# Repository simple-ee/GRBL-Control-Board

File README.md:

# GRBL-Control-Board
Custom GRBL cnc machine control board with quality in mind

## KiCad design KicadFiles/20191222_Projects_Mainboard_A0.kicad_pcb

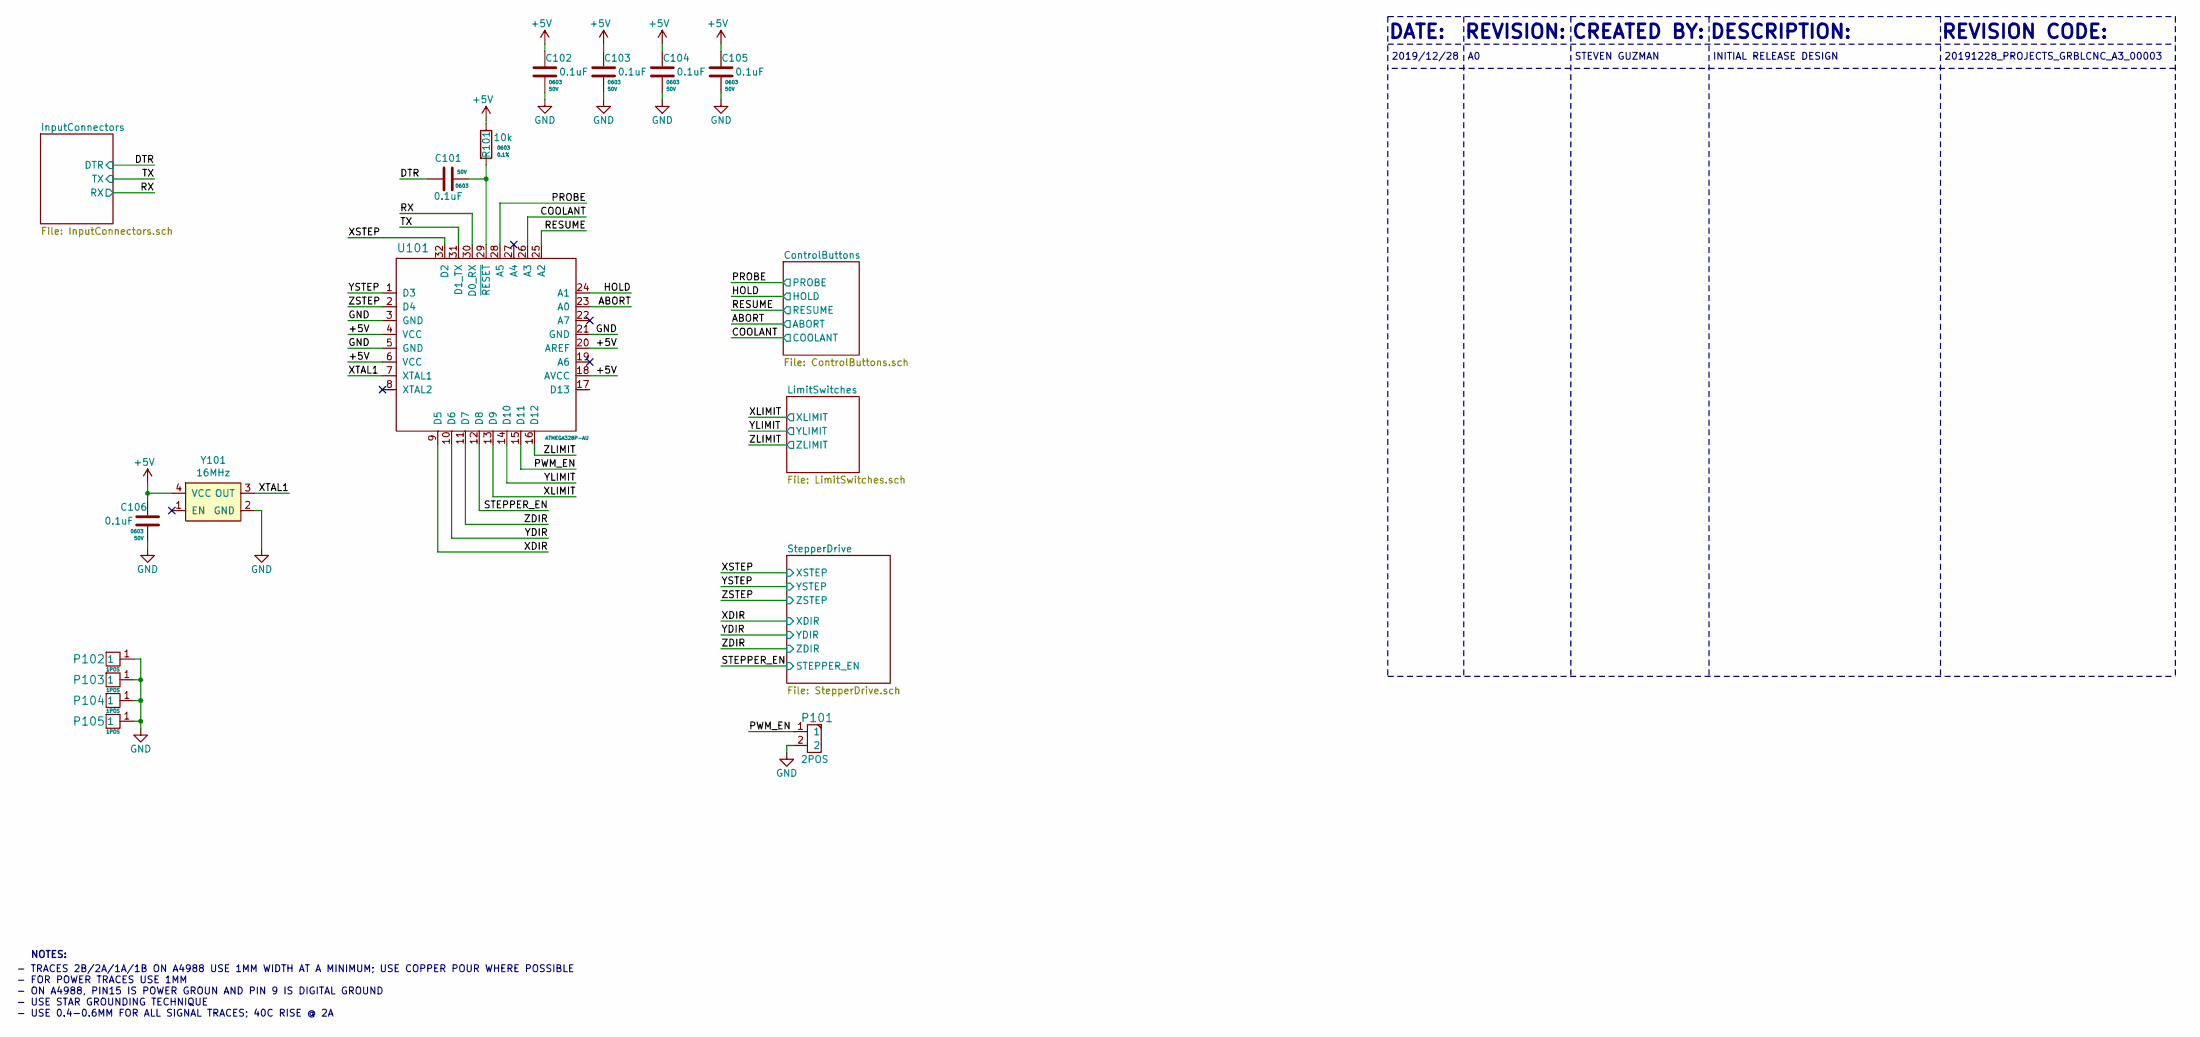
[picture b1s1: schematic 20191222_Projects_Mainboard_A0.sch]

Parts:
C101, C102, C103, C104, C105, C106: C0603C104K5RACAUTO; C_0603_Handsolder
P101: TH_2POS_2.54MM
P102, P103, P104, P105: TH_1POS_2.4MM_M2; TH_1POS_2.4MMxM2
R101: ERA-3AEB103V; R_0603_Handsolder
U101: ATMEGA328P-AU; TQFP-32
Y101: CB3-3I-16M0000; CB3

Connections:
+5V: C102.1, C103.1, C104.1, C105.1, C106.1, R101.1, U101.4 (VCC), U101.6 (VCC), U101.18 (AVCC), U101.20 (AREF), Y101.4 (VCC); also elsewhere on the board
/ABORT: U101.23 (A0); also elsewhere on the board
/COOLANT: U101.26 (A3); also elsewhere on the board
/DTR: C101.2; also elsewhere on the board
/HOLD: U101.24 (A1); also elsewhere on the board
/PROBE: U101.28 (A5); also elsewhere on the board
/PWM_EN: P101.1, U101.15 (D11)
/RESUME: U101.25 (A2); also elsewhere on the board
/RX: U101.30 (D0_RX); also elsewhere on the board
/STEPPER_EN: U101.12 (D8); also elsewhere on the board
/TX: U101.31 (D1_TX); also elsewhere on the board
/XDIR: U101.9 (D5); also elsewhere on the board
/XLIMIT: U101.13 (D9); also elsewhere on the board
/XSTEP: U101.32 (D2); also elsewhere on the board
/XTAL1: U101.7 (XTAL1), Y101.3 (OUT)
/YDIR: U101.10 (D6); also elsewhere on the board
/YLIMIT: U101.14 (D10); also elsewhere on the board
/YSTEP: U101.1 (D3); also elsewhere on the board
/ZDIR: U101.11 (D7); also elsewhere on the board
/ZLIMIT: U101.16 (D12); also elsewhere on the board
/ZSTEP: U101.2 (D4); also elsewhere on the board
GND: C102.2, C103.2, C104.2, C105.2, C106.2, P101.2, P102.1, P103.1, P104.1, P105.1, U101.3 (GND), U101.5 (GND), U101.21 (GND), Y101.2 (GND); also elsewhere on the board
unnamed: C101.1, R101.2, U101.29 (~RESET~)

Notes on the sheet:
DATE:
DESCRIPTION:
REVISION:
REVISION CODE:
2019/12/28
CREATED BY:
STEVEN GUZMAN
INITIAL RELEASE DESIGN
20191228_PROJECTS_GRBLCNC_A3_00003
- TRACES 2B/2A/1A/1B ON A4988 USE 1MM WIDTH AT A MINIMUM; USE COPPER POUR WHERE POSSIBLE - FOR POWER TRACES USE 1MM - ON A4988, PIN15 IS POWER GROUN AND PIN 9 IS DIGITAL GROUND - USE STAR GROUNDING TECHNIQUE - USE 0.4-0.6MM FOR ALL SIGNAL TRACES; 40C RISE @ 2A
NOTES:

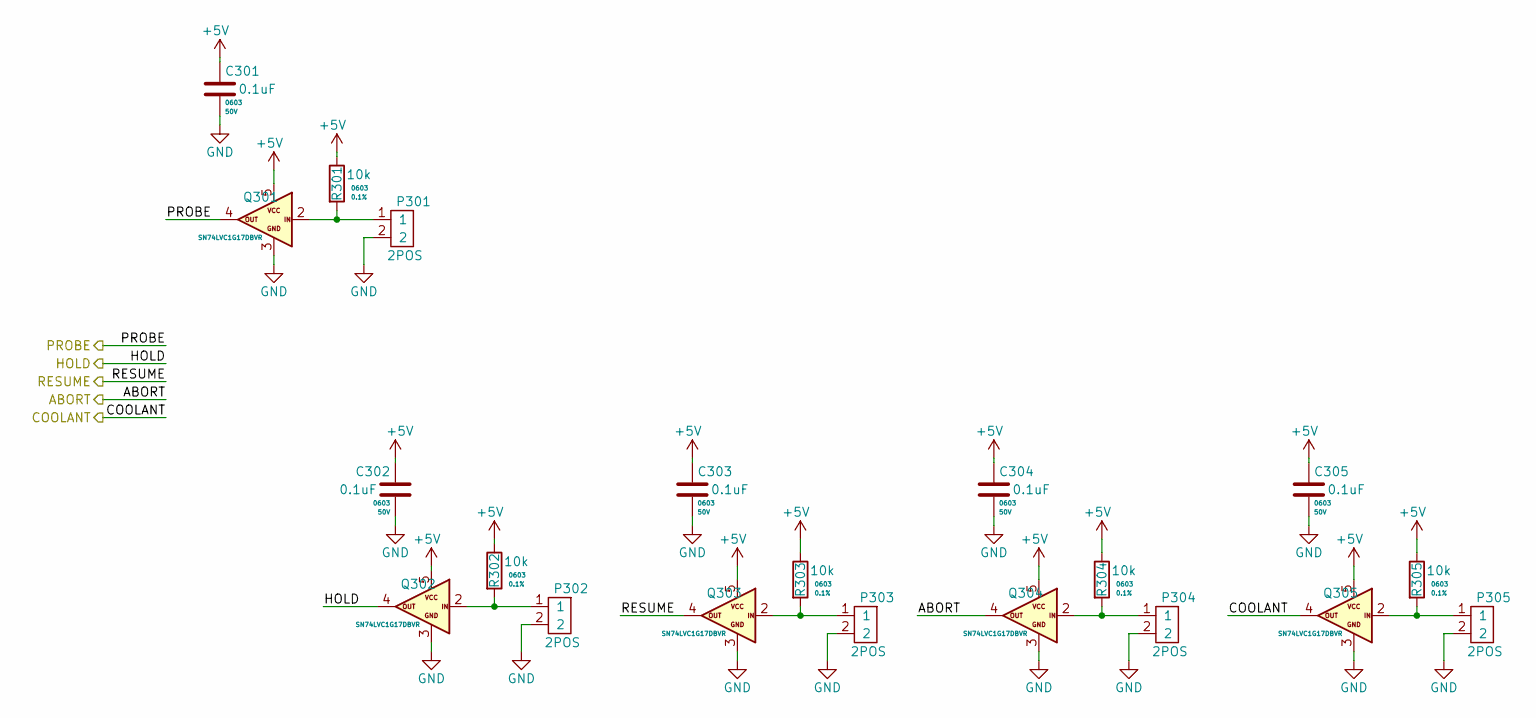
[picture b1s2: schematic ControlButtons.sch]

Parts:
C301, C302, C303, C304, C305: C0603C104K5RACAUTO; C_0603_Handsolder
P301, P302, P303, P304, P305: 2-1971798-4; 2-1971798
Q301, Q302, Q303, Q304, Q305: SN74LVC1G17DBVR; SOT-23-5_HandSoldering
R301, R302, R303, R304, R305: ERA-3AEB103V; R_0603_Handsolder

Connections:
+5V: C301.1, C302.1, C303.1, C304.1, C305.1, Q301.5, Q302.5, Q303.5, Q304.5, Q305.5, R301.1, R302.1, R303.1, R304.1, R305.1; also elsewhere on the board
/ABORT: Q304.4; also elsewhere on the board
/COOLANT: Q305.4; also elsewhere on the board
/HOLD: Q302.4; also elsewhere on the board
/PROBE: Q301.4; also elsewhere on the board
/RESUME: Q303.4; also elsewhere on the board
GND: C301.2, C302.2, C303.2, C304.2, C305.2, P301.2, P302.2, P303.2, P304.2, P305.2, Q301.3, Q302.3, Q303.3, Q304.3, Q305.3; also elsewhere on the board
unnamed: P301.1, Q301.2, R301.2
unnamed: P302.1, Q302.2, R302.2
unnamed: P303.1, Q303.2, R303.2
unnamed: P304.1, Q304.2, R304.2
unnamed: P305.1, Q305.2, R305.2

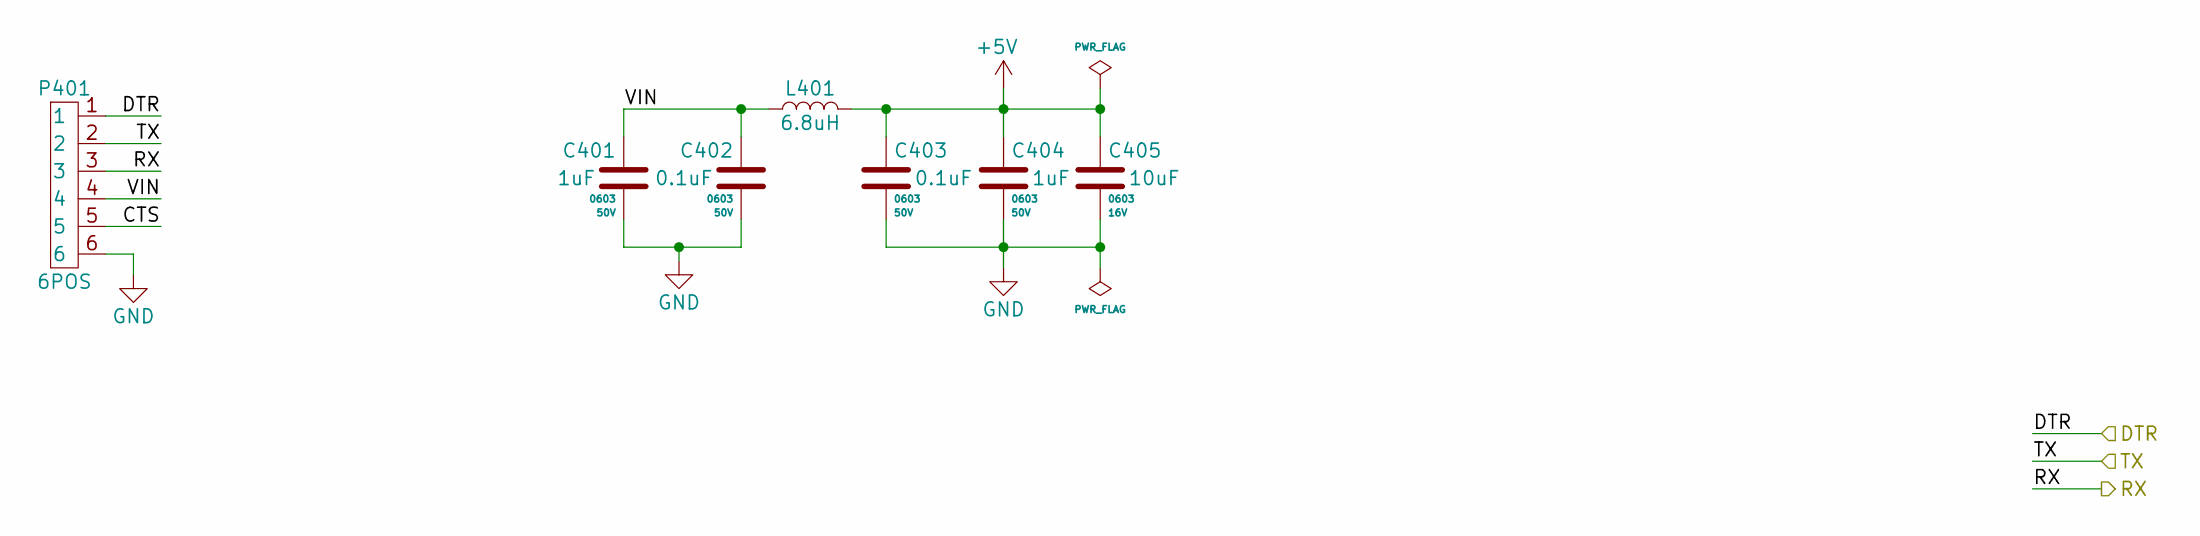
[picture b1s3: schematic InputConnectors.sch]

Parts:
C401, C404: CL10A105KB8NNNC; C_0603_Handsolder
C402, C403: C0603C104K5RACAUTO; C_0603_Handsolder
C405: CL10X106MO8NRNC; C_0603_Handsolder
L401: LPS6235-682MR_0; LPS6235
P401: M20-7910642R; M20

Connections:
+5V: C403.1, C404.1, C405.1, L401.2; also elsewhere on the board
/DTR: P401.1; also elsewhere on the board
/InputConnectors/VIN: C401.1, C402.1, L401.1, P401.4
/RX: P401.3; also elsewhere on the board
/TX: P401.2; also elsewhere on the board
GND: C401.2, C402.2, C403.2, C404.2, C405.2, P401.6; also elsewhere on the board

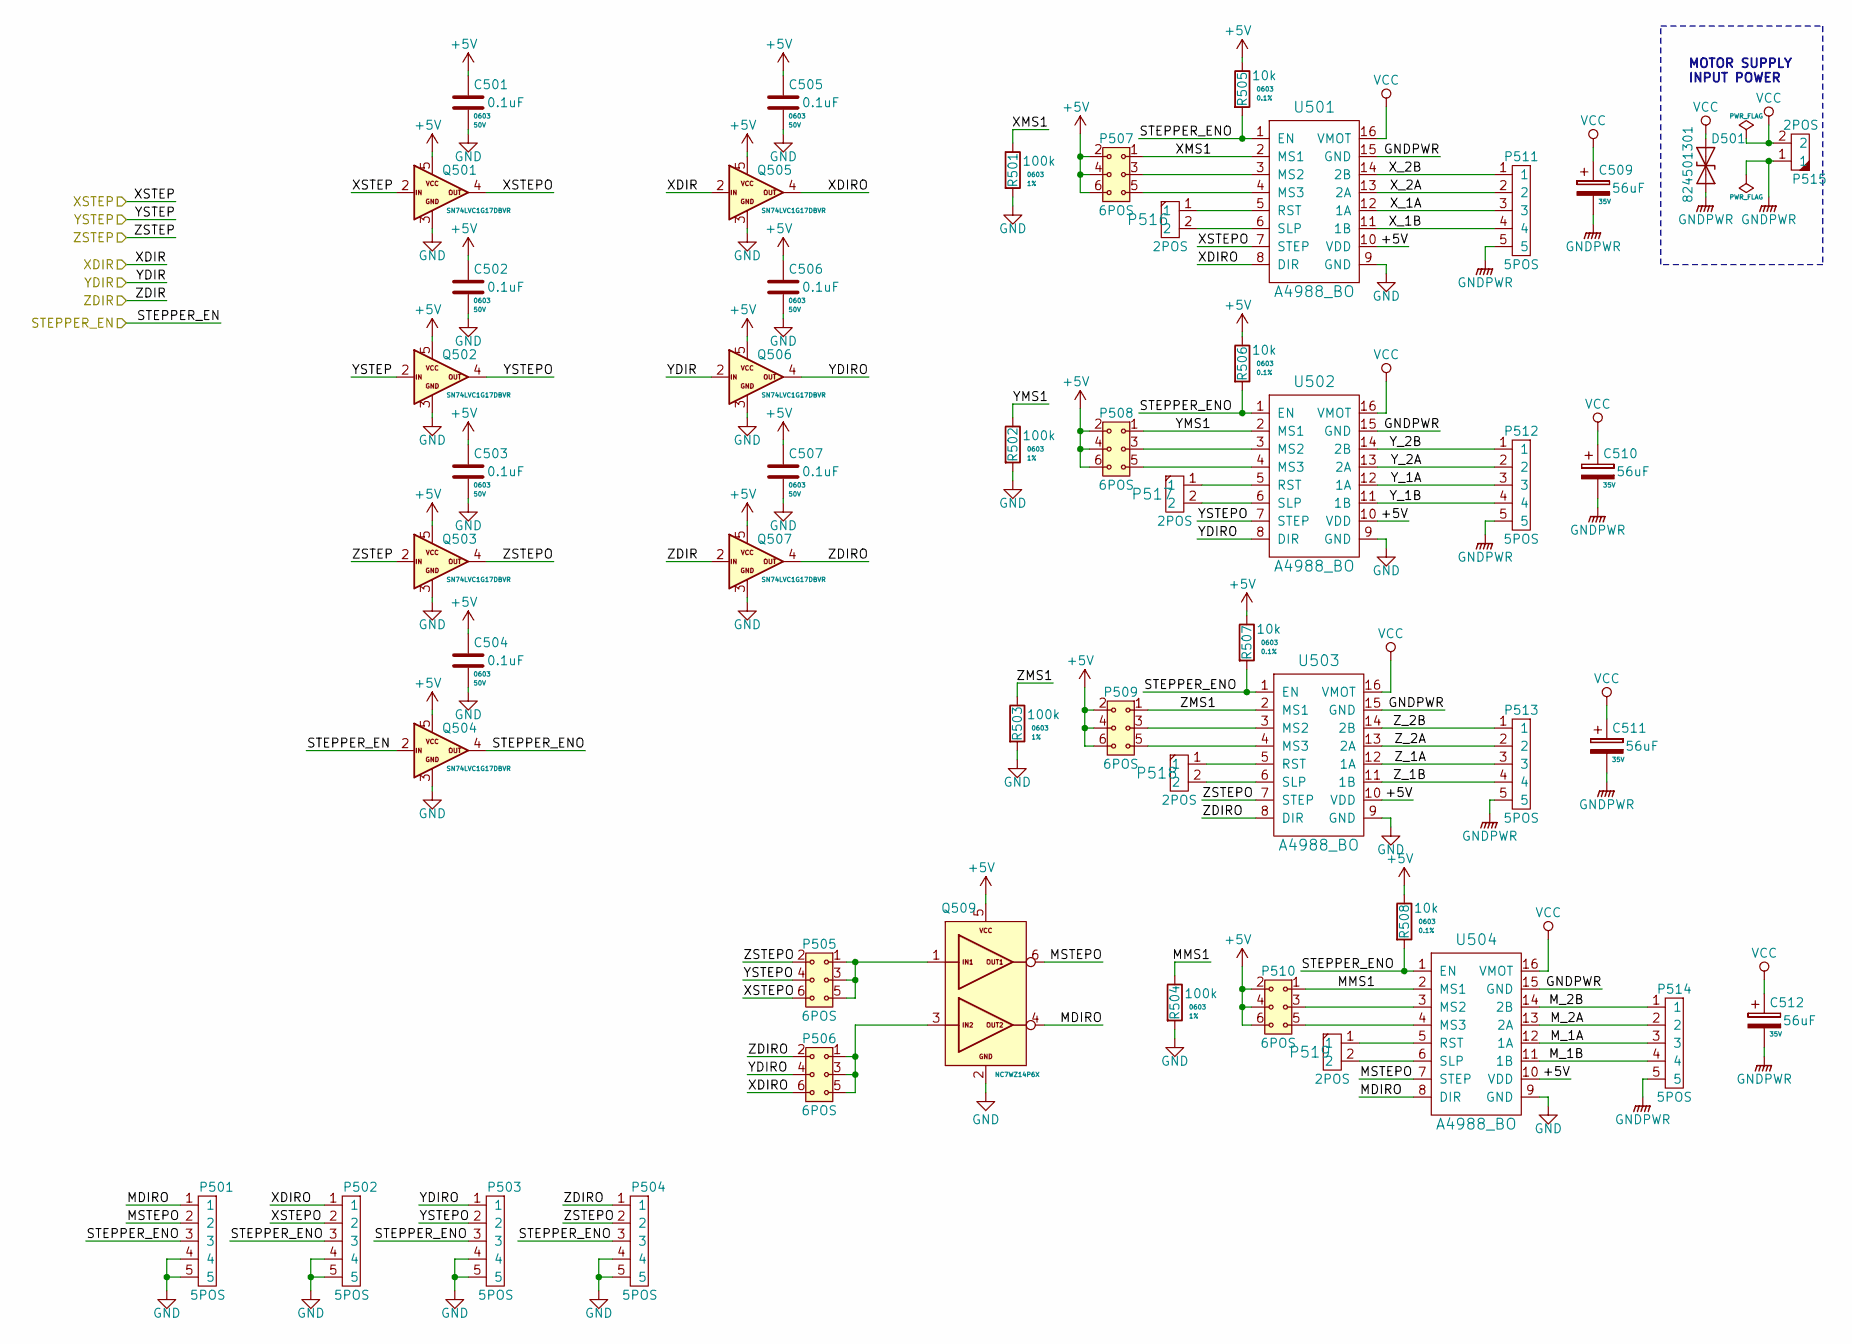
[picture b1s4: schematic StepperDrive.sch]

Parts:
C501, C502, C503, C504, C505, C506, C507: C0603C104K5RACAUTO; C_0603_Handsolder
C509, C510, C511, C512: 870055674006; Radial_D8.0mm_P3.50mm
D501: 824501301; D_SMA
P501, P502, P503, P504: 5-1971798-2
P505, P506, P507, P508, P509, P510: M20-9980346
P511, P512, P513, P514: 5-1971798-3; 5-1971798-2
P515: 1792863
P516, P517, P518, P519: TH_2POS_2.54MM
Q501, Q502, Q503, Q504, Q505, Q506, Q507: SN74LVC1G17DBVR; SOT-23-5_HandSoldering
Q509: NC7WZ14P6X; SOT-363_SC-70-6
R501, R502, R503, R504: CPF0603F100KC1; R_0603_Handsolder
R505, R506, R507, R508: ERA-3AEB103V; R_0603_Handsolder
U501, U502, U503, U504: A4988_BO; 2.54x12.7mm

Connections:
+5V: C501.1, C502.1, C503.1, C504.1, C505.1, C506.1, C507.1, P507.2, P507.4, P507.6, P508.2, P508.4, P508.6, P509.2, P509.4, P509.6, P510.2, P510.4, P510.6, Q501.5, Q502.5, Q503.5, Q504.5, Q505.5, Q506.5, Q507.5, Q509.5, R505.1, R506.1, R507.1, R508.1, U501.10 (VDD), U502.10 (VDD), U503.10 (VDD), U504.10 (VDD); also elsewhere on the board
/STEPPER_EN: Q504.2; also elsewhere on the board
/StepperDrive/MDIRO: P501.1, Q509.4, U504.8 (DIR)
/StepperDrive/MMS1: P510.1, R504.1, U504.2 (MS1)
/StepperDrive/MSTEPO: P501.2, Q509.6, U504.7 (STEP)
/StepperDrive/M_1A: P514.3, U504.12 (1A)
/StepperDrive/M_1B: P514.4, U504.11 (1B)
/StepperDrive/M_2A: P514.2, U504.13 (2A)
/StepperDrive/M_2B: P514.1, U504.14 (2B)
/StepperDrive/STEPPER_ENO: P501.3, P502.3, P503.3, P504.3, Q504.4, R505.2, R506.2, R507.2, R508.2, U501.1 (EN), U502.1 (EN), U503.1 (EN), U504.1 (EN)
/StepperDrive/XDIRO: P502.1, P506.6, Q505.4, U501.8 (DIR)
/StepperDrive/XMS1: P507.1, R501.1, U501.2 (MS1)
/StepperDrive/XSTEPO: P502.2, P505.6, Q501.4, U501.7 (STEP)
/StepperDrive/X_1A: P511.3, U501.12 (1A)
/StepperDrive/X_1B: P511.4, U501.11 (1B)
/StepperDrive/X_2A: P511.2, U501.13 (2A)
/StepperDrive/X_2B: P511.1, U501.14 (2B)
/StepperDrive/YDIRO: P503.1, P506.4, Q506.4, U502.8 (DIR)
/StepperDrive/YMS1: P508.1, R502.1, U502.2 (MS1)
/StepperDrive/YSTEPO: P503.2, P505.4, Q502.4, U502.7 (STEP)
/StepperDrive/Y_1A: P512.3, U502.12 (1A)
/StepperDrive/Y_1B: P512.4, U502.11 (1B)
/StepperDrive/Y_2A: P512.2, U502.13 (2A)
/StepperDrive/Y_2B: P512.1, U502.14 (2B)
/StepperDrive/ZDIRO: P504.1, P506.2, Q507.4, U503.8 (DIR)
/StepperDrive/ZMS1: P509.1, R503.1, U503.2 (MS1)
/StepperDrive/ZSTEPO: P504.2, P505.2, Q503.4, U503.7 (STEP)
/StepperDrive/Z_1A: P513.3, U503.12 (1A)
/StepperDrive/Z_1B: P513.4, U503.11 (1B)
/StepperDrive/Z_2A: P513.2, U503.13 (2A)
/StepperDrive/Z_2B: P513.1, U503.14 (2B)
/XDIR: Q505.2; also elsewhere on the board
/XSTEP: Q501.2; also elsewhere on the board
/YDIR: Q506.2; also elsewhere on the board
/YSTEP: Q502.2; also elsewhere on the board
/ZDIR: Q507.2; also elsewhere on the board
/ZSTEP: Q503.2; also elsewhere on the board
GND: C501.2, C502.2, C503.2, C504.2, C505.2, C506.2, C507.2, P501.4, P501.5, P502.4, P502.5, P503.4, P503.5, P504.4, P504.5, Q501.3, Q502.3, Q503.3, Q504.3, Q505.3, Q506.3, Q507.3, Q509.2, R501.2, R502.2, R503.2, R504.2, U501.9 (GND), U502.9 (GND), U503.9 (GND), U504.9 (GND); also elsewhere on the board
GNDPWR: C509.2, C510.2, C511.2, C512.2, D501.2 (A2), P511.5, P512.5, P513.5, P514.5, P515.1, U501.15 (GND), U502.15 (GND), U503.15 (GND), U504.15 (GND)
unnamed: P505.1, P505.3, P505.5, Q509.1
unnamed: P506.1, P506.3, P506.5, Q509.3
unnamed: P507.3, U501.3 (MS2)
unnamed: P507.5, U501.4 (MS3)
unnamed: P508.3, U502.3 (MS2)
unnamed: P508.5, U502.4 (MS3)
unnamed: P509.3, U503.3 (MS2)
unnamed: P509.5, U503.4 (MS3)
unnamed: P510.3, U504.3 (MS2)
unnamed: P510.5, U504.4 (MS3)
unnamed: P516.1, U501.5 (RST)
unnamed: P516.2, U501.6 (SLP)
unnamed: P517.1, U502.5 (RST)
unnamed: P517.2, U502.6 (SLP)
unnamed: P518.1, U503.5 (RST)
unnamed: P518.2, U503.6 (SLP)
unnamed: P519.1, U504.5 (RST)
unnamed: P519.2, U504.6 (SLP)
VCC: C509.1, C510.1, C511.1, C512.1, D501.1 (A1), P515.2, U501.16 (VMOT), U502.16 (VMOT), U503.16 (VMOT), U504.16 (VMOT)

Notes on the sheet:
MOTOR SUPPLY INPUT POWER

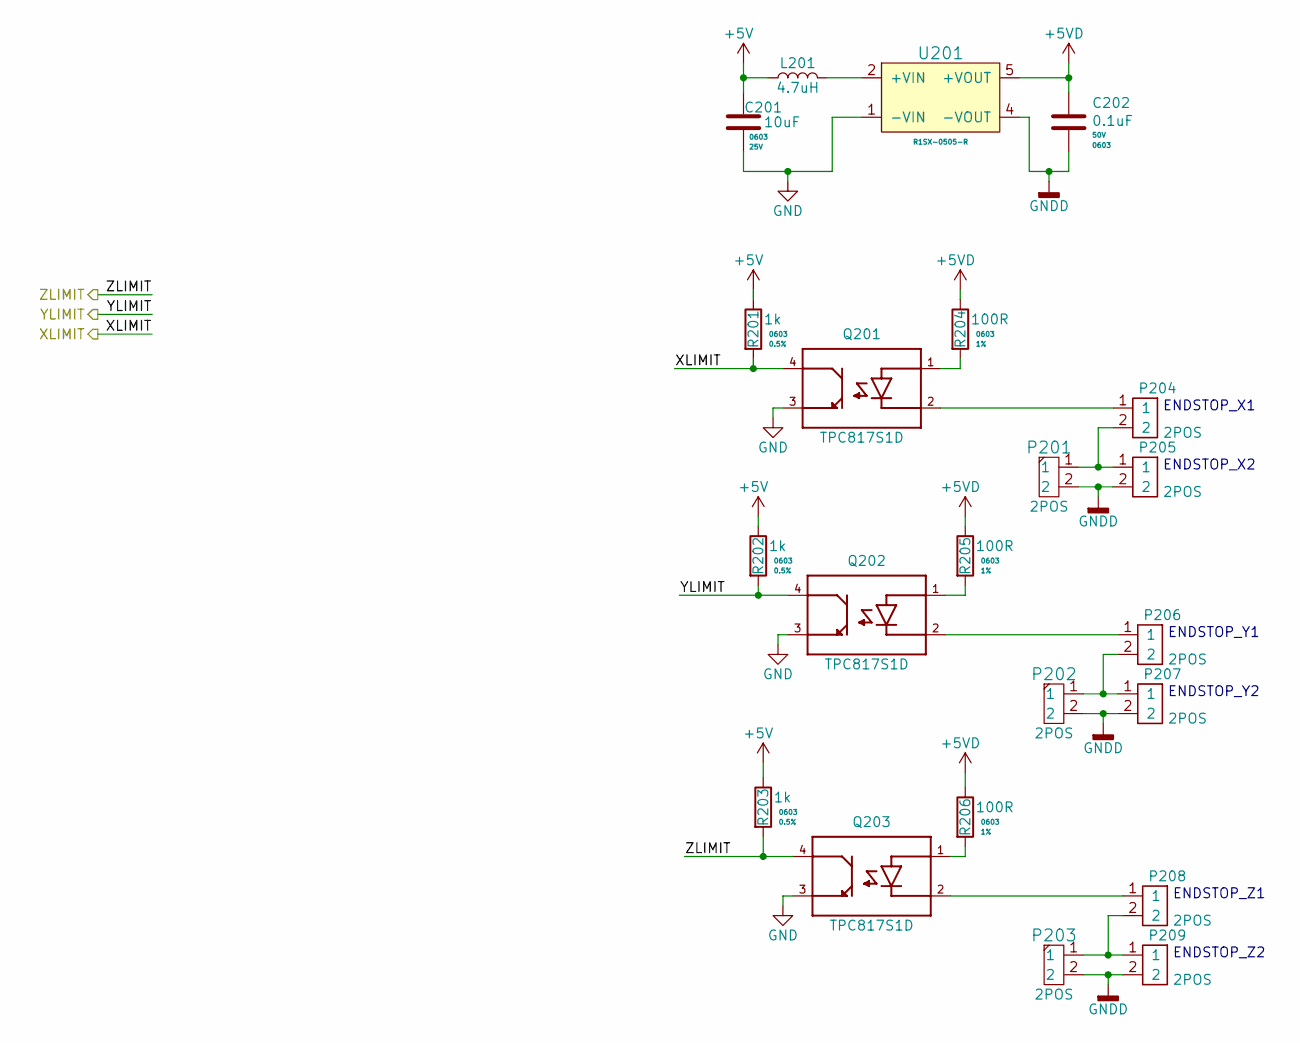
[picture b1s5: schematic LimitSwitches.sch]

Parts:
C201: ZRB18AR61E106ME01L; C_0603_Handsolder
C202: C0603C104K5RACAUTO; C_0603_Handsolder
L201: MSS5131-472ML; MSS5131
P201, P202, P203: TH_2POS_2.54MM
P204, P205, P206, P207, P208, P209: 2-1971798-2; 2-1971798
Q201, Q202, Q203: TPC817S1D; SMD-4
R201, R202, R203: RR0816P-102-D; R_0603_Handsolder
R204, R205, R206: RC0603FR-07100RL; R_0603_Handsolder
U201: R1SX-0505-R; Recom(8-smd)

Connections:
+5V: C201.1, L201.1, R201.1, R202.1, R203.1; also elsewhere on the board
+5VD: C202.1, R204.1, R205.1, R206.1, U201.5 (+VOUT)
/XLIMIT: Q201.4 (COLLECTOR), R201.2; also elsewhere on the board
/YLIMIT: Q202.4 (COLLECTOR), R202.2; also elsewhere on the board
/ZLIMIT: Q203.4 (COLLECTOR), R203.2; also elsewhere on the board
GND: C201.2, Q201.3 (EMITTER), Q202.3 (EMITTER), Q203.3 (EMITTER), U201.1 (-VIN); also elsewhere on the board
GNDD: C202.2, P201.2, P202.2, P203.2, P205.2, P207.2, P209.2, U201.4 (-VOUT)
unnamed: L201.2, U201.2 (+VIN)
unnamed: P201.1, P204.2, P205.1
unnamed: P202.1, P206.2, P207.1
unnamed: P203.1, P208.2, P209.1
unnamed: P204.1, Q201.2 (CATHODE)
unnamed: P206.1, Q202.2 (CATHODE)
unnamed: P208.1, Q203.2 (CATHODE)
unnamed: Q201.1 (ANODE), R204.2
unnamed: Q202.1 (ANODE), R205.2
unnamed: Q203.1 (ANODE), R206.2

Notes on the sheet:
ENDSTOP_X1
ENDSTOP_X2
ENDSTOP_Y1
ENDSTOP_Y2
ENDSTOP_Z1
ENDSTOP_Z2

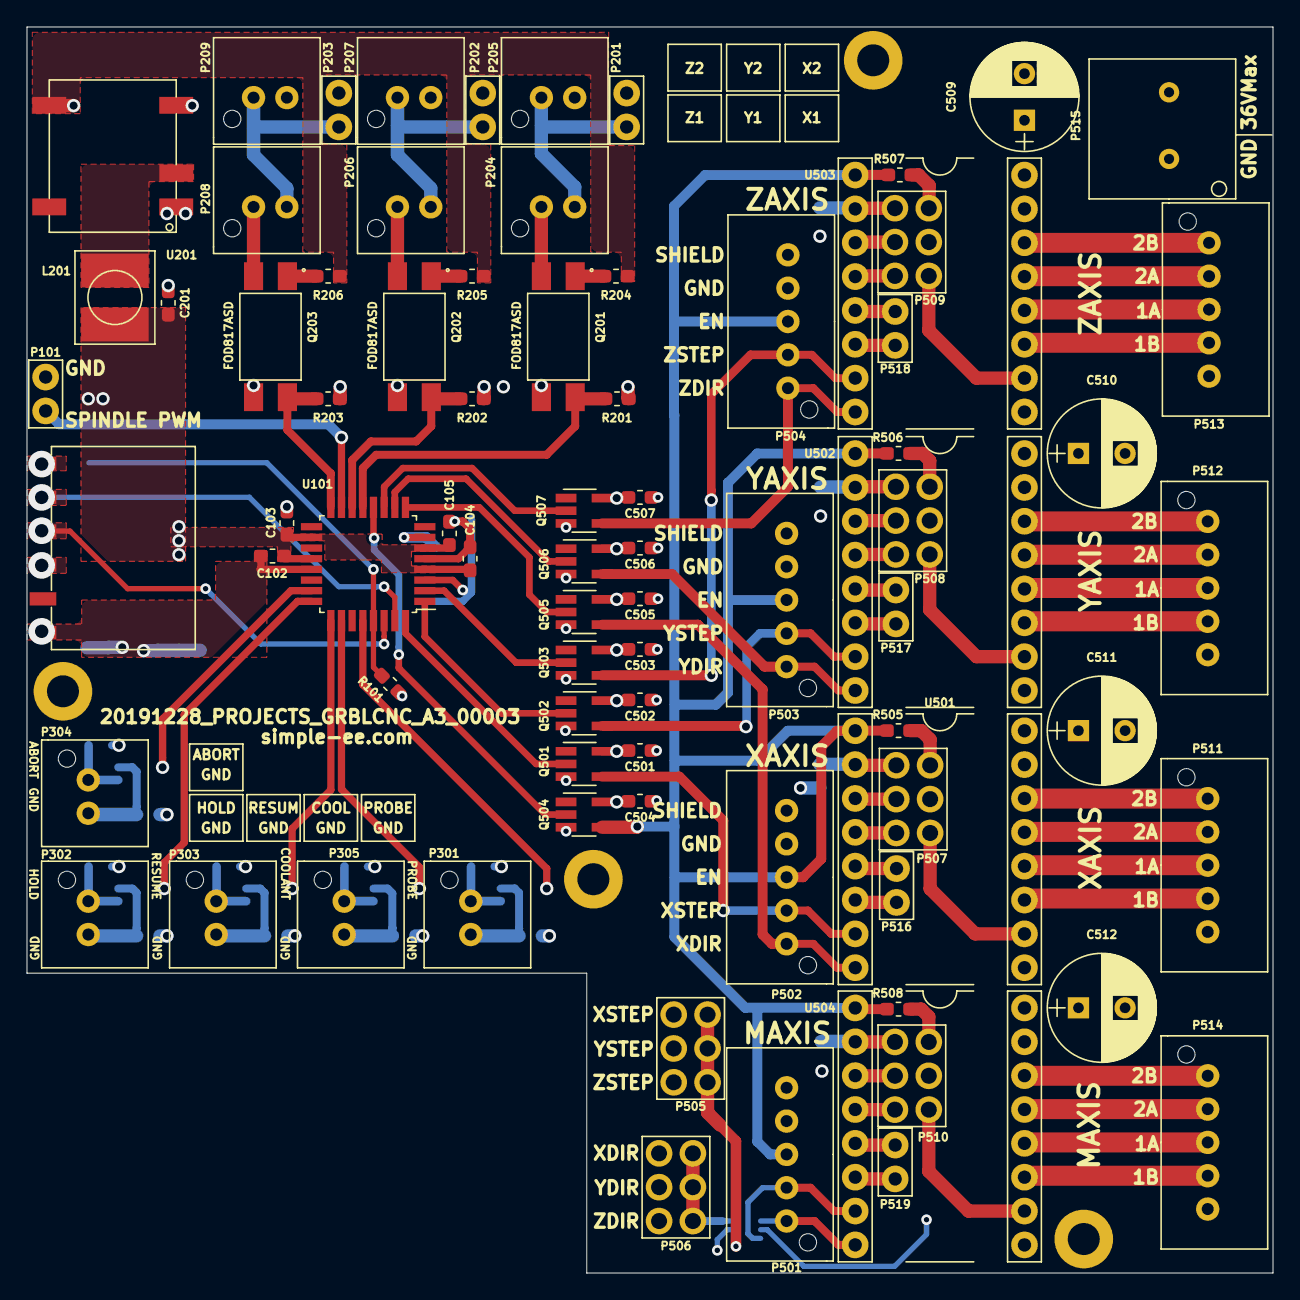
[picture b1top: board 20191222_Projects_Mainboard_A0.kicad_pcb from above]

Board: 4 copper layers, 93.5 x 93.5 mm, 114 parts (0 on the bottom side), 90 nets.
